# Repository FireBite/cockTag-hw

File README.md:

# cockTag-hw
Proudly challenging the well-established Polish tracking tag industry

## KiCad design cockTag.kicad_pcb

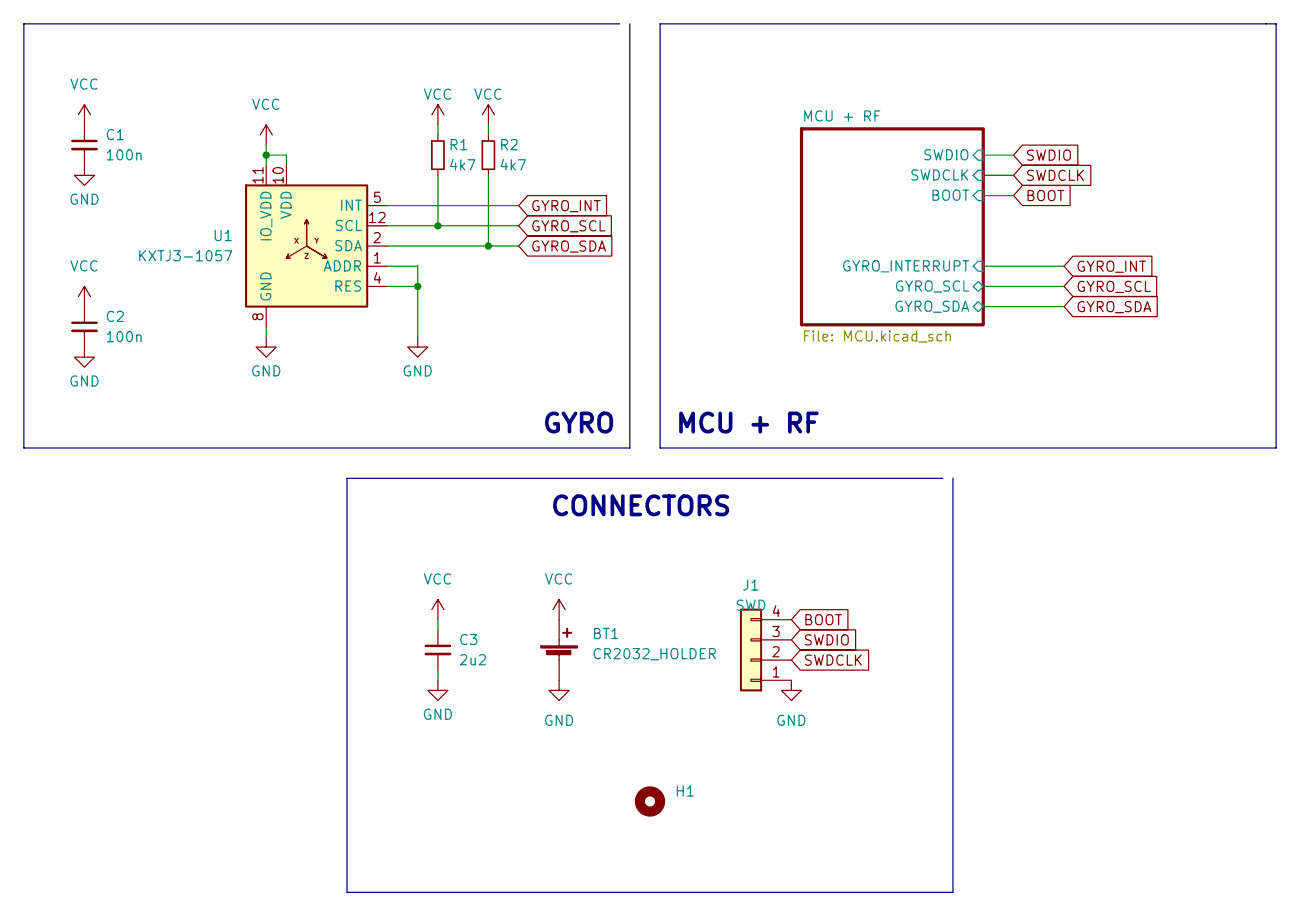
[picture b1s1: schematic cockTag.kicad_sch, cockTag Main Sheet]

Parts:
BT1: CR2032_HOLDER; MY-2032-01; LCSC C964824
C1, C2: 100n; C_0402_1005Metric; LCSC C41851
C3: 2u2; C_0603_1608Metric; LCSC C5189830
H1: MountingHole_Pad; MountingHole_2.2mm_M2
J1: SWD; PinHeader_1x04_P1.27mm_Vertical; LCSC C2935944
R1, R2: 4k7; R_0402_1005Metric; LCSC C25940
U1: KXTJ3-1057; Kionix_LGA-12_2x2mm_P0.5mm_LayoutBorder2x4y; LCSC C442603

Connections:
BOOT: J1.4; also elsewhere on the board
GND: BT1.2 (-), C1.2, C2.2, C3.2, J1.1, U1.1 (ADDR), U1.4 (RES), U1.6 (GND), U1.8 (GND), U1.9 (GND); also elsewhere on the board
GYRO_INT: U1.5 (INT); also elsewhere on the board
GYRO_SCL: R1.2, U1.12 (SCL); also elsewhere on the board
GYRO_SDA: R2.2, U1.2 (SDA); also elsewhere on the board
SWDCLK: J1.2; also elsewhere on the board
SWDIO: J1.3; also elsewhere on the board
VCC: BT1.1 (+), C1.1, C2.1, C3.1, R1.1, R2.1, U1.3 (IO_VDD), U1.7 (VDD), U1.10 (VDD), U1.11 (IO_VDD); also elsewhere on the board

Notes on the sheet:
CONNECTORS
MCU + RF
GYRO

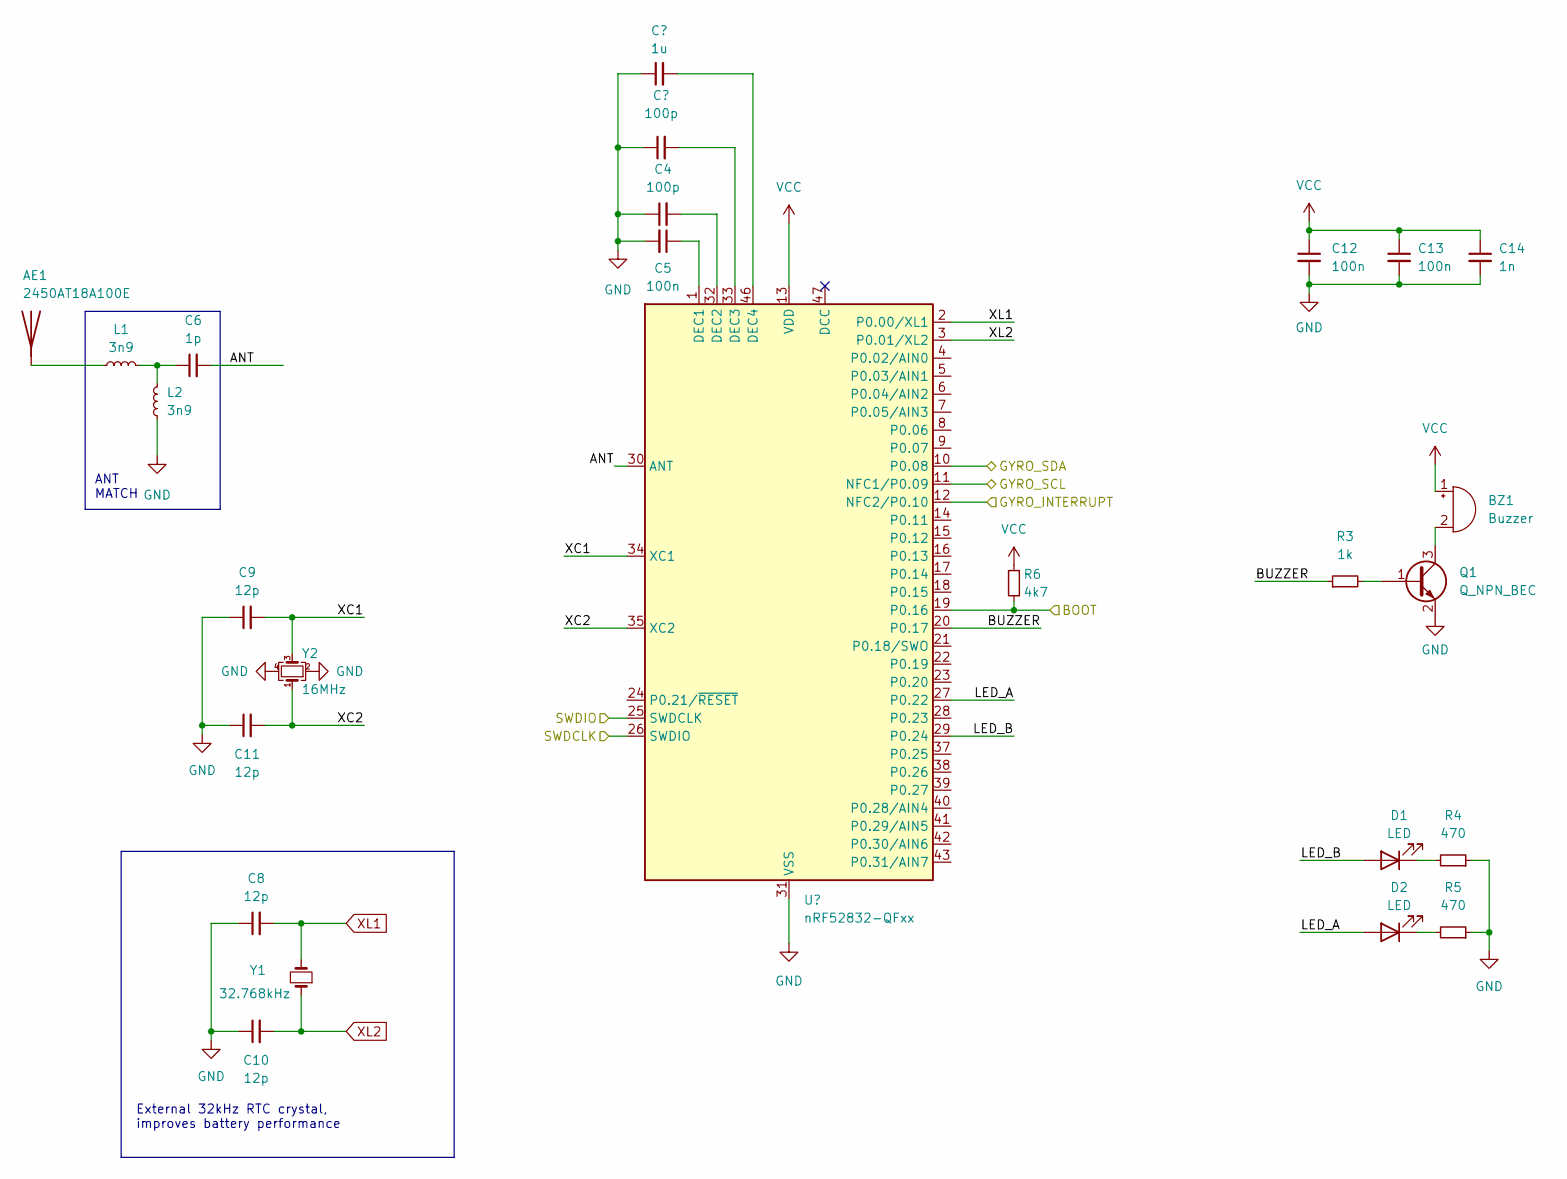
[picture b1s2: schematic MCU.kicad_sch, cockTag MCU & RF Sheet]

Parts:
AE1: 2450AT18A100E; Johanson_2450AT18x100; LCSC C89334
BZ1: Buzzer; PUIAudio_SMT_0825_S_4_R; LCSC C409827
C4: 100p; C_0402_1005Metric
C5, C12, C13: 100n; C_0402_1005Metric; LCSC C41851
C6: 1p; C_0402_1005Metric; LCSC C710646
C8, C9, C10, C11: 12p; C_0402_1005Metric; LCSC C106201
C14: 1n; C_0402_1005Metric; LCSC C575438
D1, D2: LED; LED_0402_1005Metric
L1, L2: 3n9; L_0402_1005Metric; LCSC C961331
Q1: Q_NPN_BEC; SOT-323_SC-70; LCSC C553063
R3: 1k; R_0402_1005Metric; LCSC C2906899
R4, R5: 470; R_0402_1005Metric
R6: 4k7; R_0402_1005Metric; LCSC C25940
Y1: 32.768kHz; Crystal_SMD_3215-2Pin_3.2x1.5mm; LCSC C32346
Y2: 16MHz; Crystal_SMD_3225-4Pin_3.2x2.5mm; LCSC C362342

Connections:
/MCU + RF/ANT: C6.2; also elsewhere on the board
/MCU + RF/BUZZER: R3.1; also elsewhere on the board
/MCU + RF/LED_A: D2.2 (A); also elsewhere on the board
/MCU + RF/LED_B: D1.2 (A); also elsewhere on the board
/MCU + RF/XC1: C9.2, Y2.3; also elsewhere on the board
/MCU + RF/XC2: C11.2, Y2.1; also elsewhere on the board
BOOT: R6.2; also elsewhere on the board
GND: C4.1, C5.2, C8.1, C9.1, C10.1, C11.1, C12.2, C13.2, C14.2, L2.1, Q1.2 (E), R4.1, R5.1, Y2.2, Y2.4; also elsewhere on the board
unnamed: AE1.1 (A), L1.1
unnamed: BZ1.2 (+), Q1.3 (C)
unnamed 13: C4.2; also elsewhere on the board
unnamed 14: C5.1; also elsewhere on the board
unnamed: C6.1, L1.2, L2.2
unnamed: D1.1 (K), R4.2
unnamed: D2.1 (K), R5.2
unnamed: Q1.1 (B), R3.2
VCC: BZ1.1 (-), C12.1, C13.1, C14.1, R6.1; also elsewhere on the board
XL1: C8.2, Y1.2; also elsewhere on the board
XL2: C10.2, Y1.1; also elsewhere on the board

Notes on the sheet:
ANT MATCH
External 32kHz RTC crystal, improves battery performance

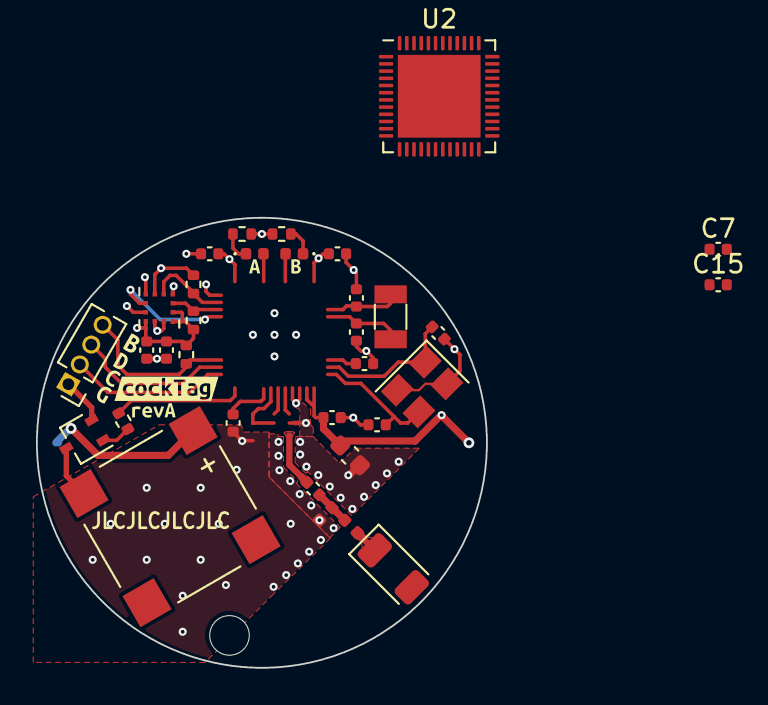
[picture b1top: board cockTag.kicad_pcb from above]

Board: 4 copper layers, 25.0 x 25.0 mm, 43 parts (1 on the bottom side), 26 nets.

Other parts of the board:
C7: 1u; C_0402_1005Metric
C15: 100p; C_0402_1005Metric
U2: nRF52832-QFxx; QFN-48-1EP_6x6mm_P0.4mm_EP4.6x4.6mm
kibuzzard-6367CCAB: G***; kibuzzard-6367CCAB
kibuzzard-6367CCB8: G***; kibuzzard-6367CCB8
kibuzzard-6367CCBF: G***; kibuzzard-6367CCBF
kibuzzard-6367CCCA: G***; kibuzzard-6367CCCA
kibuzzard-6367CDC3: G***; kibuzzard-6367CDC3
kibuzzard-6367CE4A: G***; kibuzzard-6367CE4A
kibuzzard-6367D1D3: G***; kibuzzard-6367D1D3
kibuzzard-6367D1E2: G***; kibuzzard-6367D1E2

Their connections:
/MCU + RF/ANT: U2.30 (ANT); also elsewhere on the board
/MCU + RF/BUZZER: U2.20 (P0.17); also elsewhere on the board
/MCU + RF/LED_A: U2.27 (P0.22); also elsewhere on the board
/MCU + RF/LED_B: U2.29 (P0.24); also elsewhere on the board
/MCU + RF/XC1: U2.34 (XC1); also elsewhere on the board
/MCU + RF/XC2: U2.35 (XC2); also elsewhere on the board
BOOT: U2.19 (P0.16); also elsewhere on the board
GND: C7.1, C15.1, U2.31 (VSS), U2.45 (VSS), U2.49 (VSS); also elsewhere on the board
GYRO_INT: U2.12 (NFC2/P0.10); also elsewhere on the board
GYRO_SCL: U2.11 (NFC1/P0.09); also elsewhere on the board
GYRO_SDA: U2.10 (P0.08); also elsewhere on the board
unnamed 13: U2.32 (DEC2); also elsewhere on the board
unnamed 14: U2.1 (DEC1); also elsewhere on the board
unnamed: C7.2, U2.46 (DEC4)
unnamed: C15.2, U2.33 (DEC3)
SWDCLK: U2.26 (SWDIO); also elsewhere on the board
SWDIO: U2.25 (SWDCLK); also elsewhere on the board
VCC: U2.13 (VDD), U2.36 (VDD), U2.48 (VDD); also elsewhere on the board
XL1: U2.2 (P0.00/XL1); also elsewhere on the board
XL2: U2.3 (P0.01/XL2); also elsewhere on the board

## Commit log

2022-11-06 Add schematic
2022-11-09 feat: Assign LCSC ids to the schematic
2022-11-09 Minor PCB layout fix
2022-11-09 Change CR2032 header LCSC id
2022-11-09 Add outputs
2023-02-21 Change schematic to NRF52832
